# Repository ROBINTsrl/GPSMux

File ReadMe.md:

# GPSMux

This board and related firmware can be used to switch between two serial NMEA GPS feed based on fix status.
The resulting feed is transmitted over a third serial line with RS232 levels.
The board is designed around [Cypress](https://www.cypress.com/) PSoC CY8C27143.

PCB has been designed with [KiCAD](https://www.kicad.org/).

## Firmware

The project firmware requires Cypress [PSoC Designer 5.4](https://www.cypress.com/documentation/software-and-drivers/psoc-designer-54-sp1) to be compiled.

#

Live long and prosper!

That's all folks.

By[t]e{s} Weirdgyn

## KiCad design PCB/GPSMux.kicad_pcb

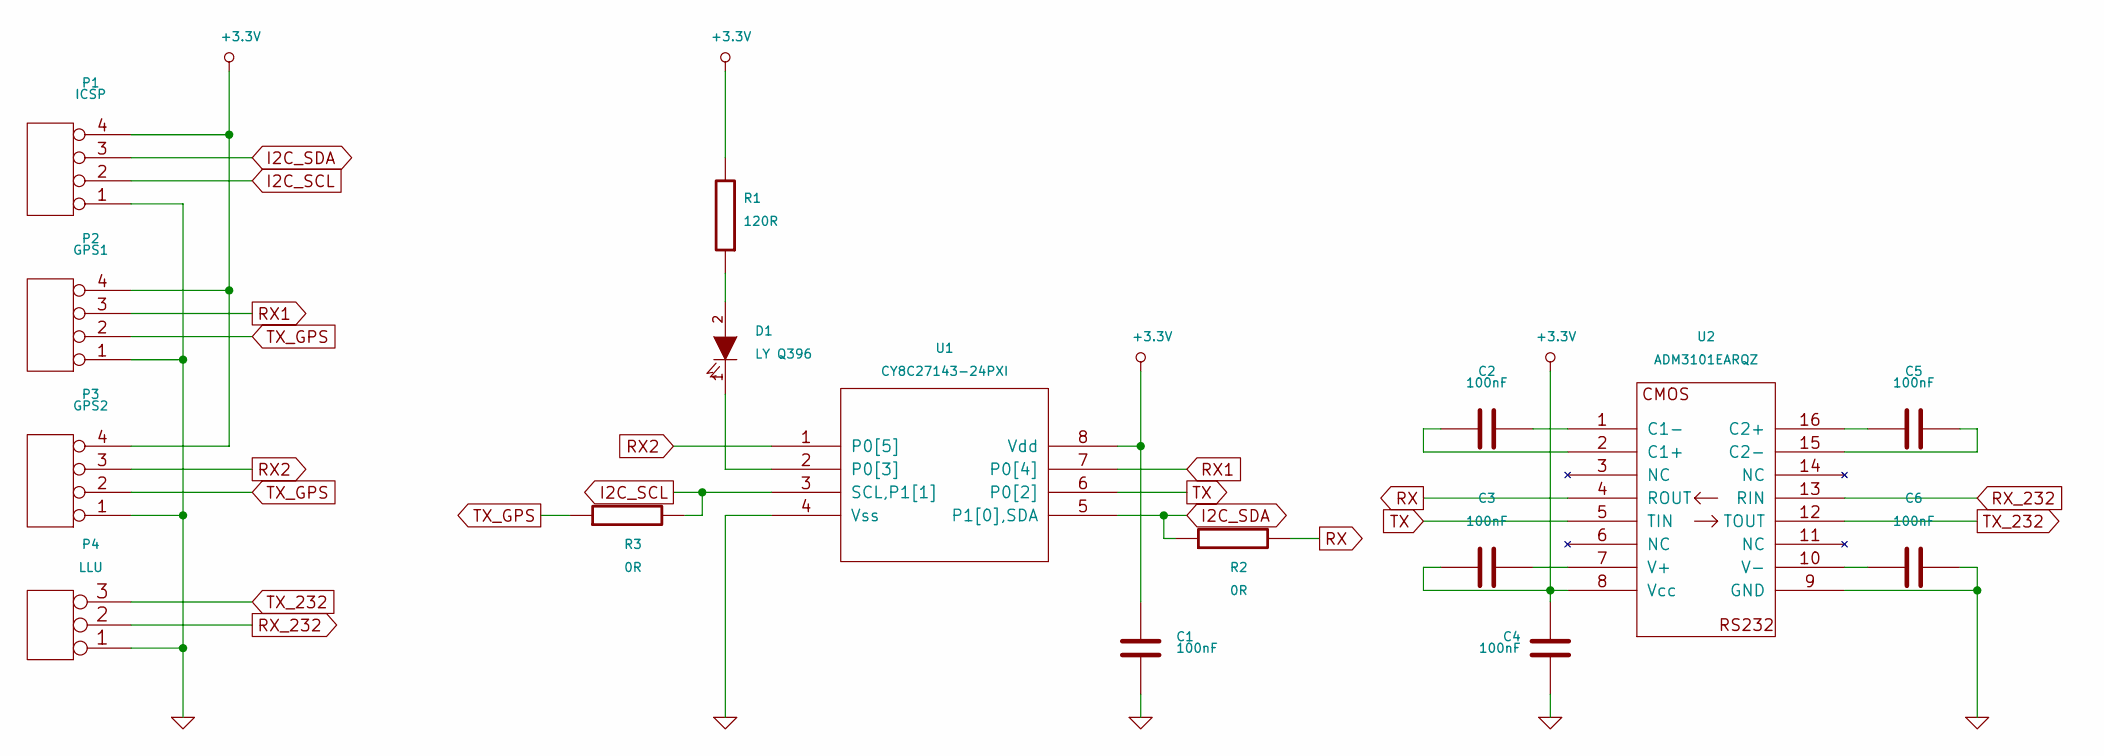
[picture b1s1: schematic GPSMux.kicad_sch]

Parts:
C1, C2, C3, C4, C5, C6: 100nF; C_0603; mpn 06035C104K4T2A; Digikey 478-5309-1-ND
D1: LY Q396; LED_0603_HandSoldering; mpn LY Q396; Digikey 475-3467-1-ND
P1: ICSP; 53261-0471; mpn 53261-0471; Digikey WM7622CT-ND
P2: GPS1; 53261-0471; mpn 53261-0471; Digikey WM7622CT-ND
P3: GPS2; 53261-0471; mpn 53261-0471; Digikey WM7622CT-ND
P4: LLU; 53261-0371; mpn 53261-0371; Digikey WM7621CT-ND
R1: 120R; R_0603_HandSoldering; mpn CRCW0603120RFKEA; Digikey 541-120HCT-ND
R2, R3: 0R; R_0603_HandSoldering; mpn CRCW06030000Z0EB; Digikey 541-4013-1-ND
U1: CY8C27143-24PXI; DIP-8_W10.16mm; mpn CY8C27143-24PXI; Digikey 428-1593-ND
U2: ADM3101EARQZ; QSOP16; mpn ADM3101EARQZ; Digikey ADM3101EARQZ-REELCT-ND

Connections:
+3.3V: C1.1, C3.2, C4.1, P1.4, P2.4, P3.4, R1.2, U1.8 (Vdd), U2.8 (Vcc)
GND: C1.2, C4.2, C6.1, P1.1, P2.1, P3.1, P4.1, U1.4 (Vss), U2.9 (GND)
I2C_SCL: P1.2, R3.2, U1.3 (SCL,P1[1])
I2C_SDA: P1.3, R2.1, U1.5 (P1[0],SDA)
unnamed: C2.1, U2.1 (C1-)
unnamed: C2.2, U2.2 (C1+)
unnamed: C3.1, U2.7 (V+)
unnamed: C5.1, U2.16 (C2+)
unnamed: C5.2, U2.15 (C2-)
unnamed: C6.2, U2.10 (V-)
unnamed: D1.1 (K), U1.2 (P0[3])
unnamed: D1.2 (A), R1.1
RX: R2.2, U2.4 (ROUT)
RX1: P2.3, U1.7 (P0[4])
RX2: P3.3, U1.1 (P0[5])
RX_232: P4.2 (PM), U2.13 (RIN)
TX: U1.6 (P0[2]), U2.5 (TIN)
TX_232: P4.3, U2.12 (TOUT)
TX_GPS: P2.2, P3.2, R3.1

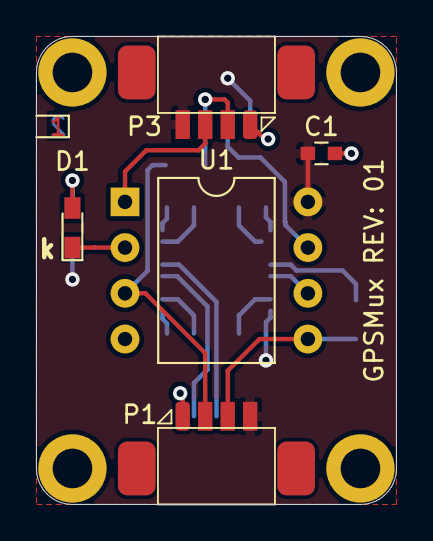
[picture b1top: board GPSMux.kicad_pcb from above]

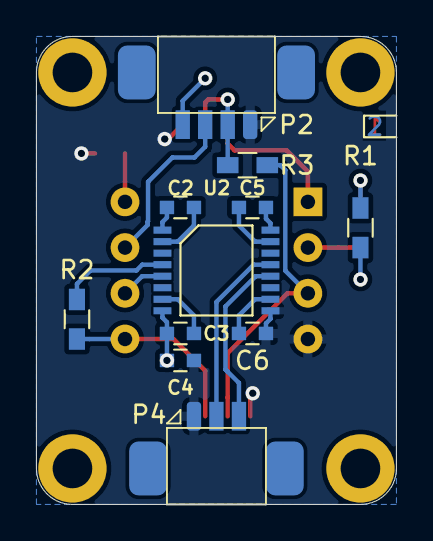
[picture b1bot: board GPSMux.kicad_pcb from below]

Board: 2 copper layers, 20.0 x 26.0 mm, 16 parts (11 on the bottom side), 19 nets.

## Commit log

2021-05-12 Fist command
2021-05-12 Add ReadMe.md
2021-05-12 Cleanup
2021-05-12 Create LICENSE
2021-05-12 Fix 3d components paths
2021-05-12 Updated BOM, zone settings modified, components 3d updated
2021-05-13 Modified folders tree
2021-05-13 Update BOM
    Revert on .tsv
2021-05-13 Updated BOM
2021-05-14 Update BOM
2024-09-24 Updated to kicad 8.0
